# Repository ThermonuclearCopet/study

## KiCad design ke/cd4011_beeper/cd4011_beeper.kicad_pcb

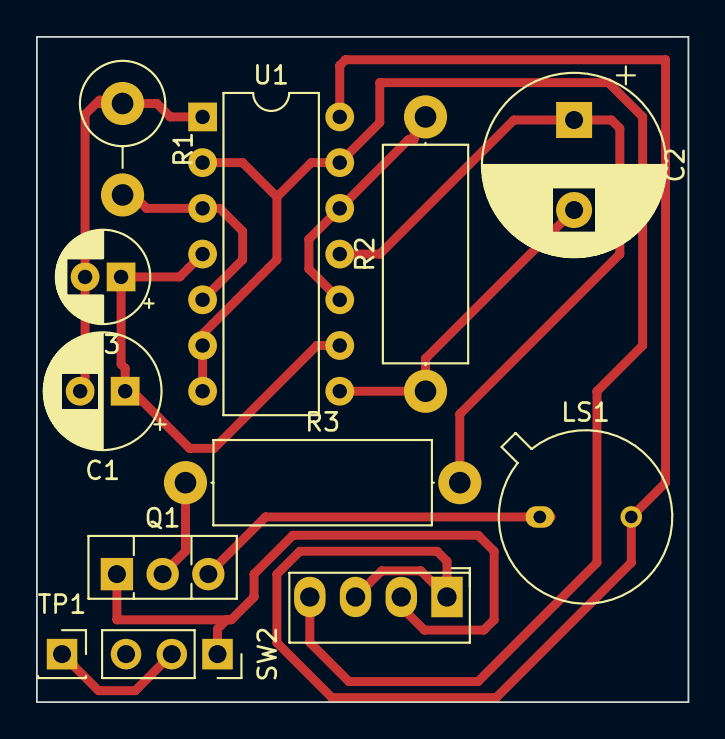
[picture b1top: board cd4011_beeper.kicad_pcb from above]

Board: 2 copper layers, 36.2 x 37.0 mm, 12 parts (0 on the bottom side), 12 nets.

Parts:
C1: 10uf; CP_Radial_D6.3mm_P2.50mm
C2: 470uf; CP_Radial_D10.0mm_P5.00mm
C3: 2.2uf; CP_Radial_D5.0mm_P2.00mm
LS1: Speaker; TO-5-2
PS1: MEE3S1205SC; Converter_DCDC_Murata_MEE3SxxxxSC_THT
Q1: NPN; TO-126-3_Vertical
R1: 150k; R_Axial_DIN0414_L11.9mm_D4.5mm_P5.08mm_Vertical
R2: 1.5k; R_Axial_DIN0414_L11.9mm_D4.5mm_P15.24mm_Horizontal
R3: 10k; R_Axial_DIN0414_L11.9mm_D4.5mm_P15.24mm_Horizontal
SW2: SW_Nidec_CAS-120A1; PinSocket_1x03_P2.54mm_Vertical
TP1: TestPoint; PinSocket_1x01_P2.54mm_Vertical
U1: 4011; DIP-14_W7.62mm

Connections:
+5V: PS1.4 (+Vout), U1.2, U1.6, U1.7 (VSS), U1.13
+15V: SW2.2 (B), TP1.1
GND: LS1.2, PS1.1 (-Vin), PS1.3 (-Vout), U1.14 (VDD)
unnamed: C1.1, C3.1, U1.4, U1.9
unnamed: C1.2, C3.2, R1.1, U1.1
unnamed: C2.1, R3.2, U1.11
unnamed: C2.2, R2.1, U1.8
unnamed: PS1.2 (+Vin), Q1.1 (C), SW2.1 (C)
unnamed: Q1.2 (B), R3.1
unnamed: LS1.1, Q1.3 (E)
unnamed: R1.2, U1.3, U1.5
unnamed: R2.2, U1.10, U1.12

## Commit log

2024-09-18 restructured all subjects to one repo and added nm_lab_1
2024-09-18 restructured all subjects to one repo and added nm_lab_1 v2
2024-09-18 update v3
2024-09-19 restructured num_methods and added lab_2 nm
2024-10-07 IDK files (by vva)
2024-10-10 fix: fixed web lab 3
2024-10-31 file flow
2024-11-21 7 lab bugs
2024-11-30 fileflow
